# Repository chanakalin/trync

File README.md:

# trync
**trync** is an open source IoT powered application for logging environmetal conditions and maintaining saturated environmental conditions in medical storage and transporation.

More details available at [trync.blogspot.com](https://trync.blogspot.com)

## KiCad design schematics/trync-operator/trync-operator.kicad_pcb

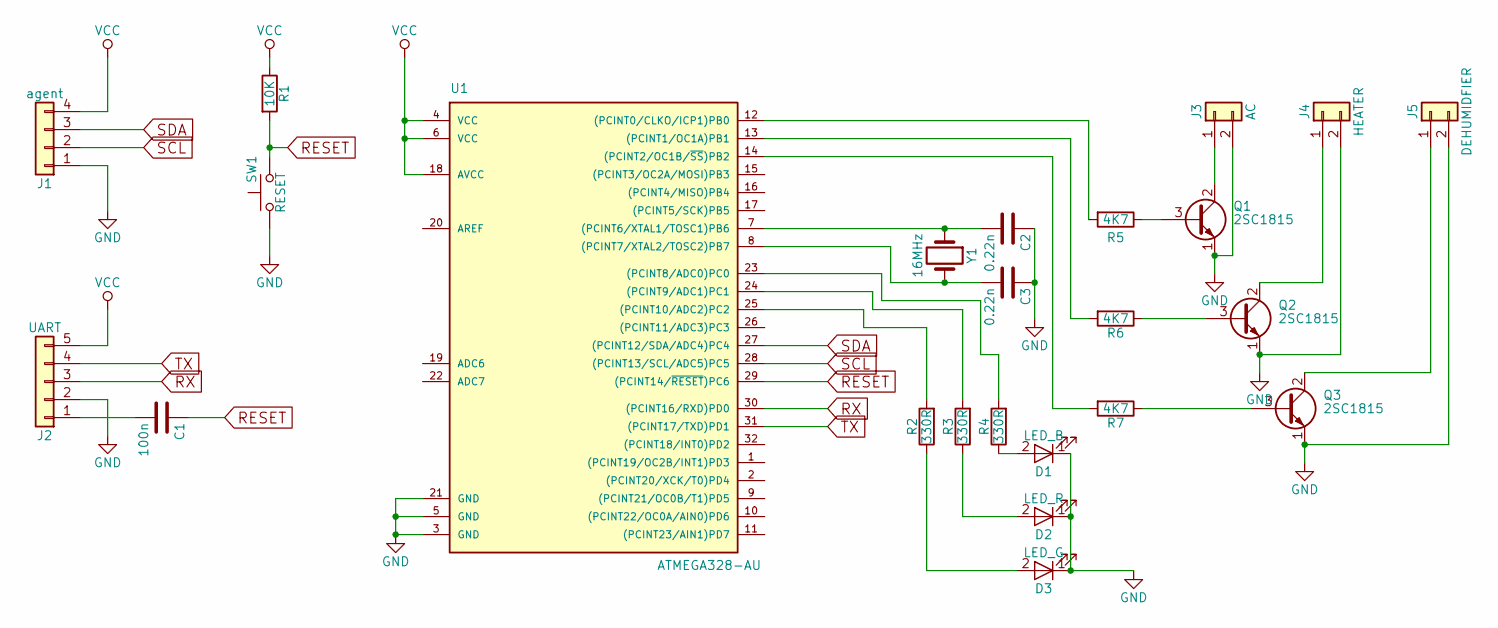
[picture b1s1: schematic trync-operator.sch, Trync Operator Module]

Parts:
C1: 100n; C_Disc_D4.3mm_W1.9mm_P5.00mm
C2, C3: 0.22n; C_Disc_D3.8mm_W2.6mm_P2.50mm
D1: LED_B; LED_0805_HandSoldering
D2: LED_R; LED_0805_HandSoldering
D3: LED_G; LED_0805_HandSoldering
J1: agent; Pin_Header_Straight_1x04_Pitch2.54mm
J2: UART; Pin_Header_Straight_1x05_Pitch2.54mm
J3: AC; Pin_Header_Angled_1x02_Pitch2.54mm
J4: HEATER; Pin_Header_Angled_1x02_Pitch2.54mm
J5: DEHUMIDFIER; Pin_Header_Angled_1x02_Pitch2.54mm
Q1, Q2, Q3: 2SC1815; TO-92_Molded_Narrow
R1: 10K; R_0805_HandSoldering
R2, R3, R4: 330R; R_0805_HandSoldering
R5, R6, R7: 4K7; R_0805_HandSoldering
SW1: RESET; SW_PUSH_6mm
U1: ATMEGA328-AU; TQFP-32_7x7mm_Pitch0.8mm
Y1: 16MHz; Crystal_HC52-8mm_Vertical

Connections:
GND: C2.1, C3.1, D1.1 (K), D2.1 (K), D3.1 (K), J1.1, J2.2, J3.2, J4.2, J5.2, Q1.1 (E), Q2.1 (E), Q3.1 (E), SW1.1, U1.3 (GND), U1.5 (GND), U1.21 (GND)
unnamed: C1.2, J2.1
unnamed: C2.2, U1.7 ((PCINT6/XTAL1/TOSC1)PB6), Y1.1
unnamed: C3.2, U1.8 ((PCINT7/XTAL2/TOSC2)PB7), Y1.2
unnamed: D1.2 (A), R4.1
unnamed: D2.2 (A), R3.1
unnamed: D3.2 (A), R2.1
unnamed: J3.1, Q1.2 (C)
unnamed: J4.1, Q2.2 (C)
unnamed: J5.1, Q3.2 (C)
unnamed: Q1.3 (B), R5.1
unnamed: Q2.3 (B), R6.1
unnamed: Q3.3 (B), R7.1
unnamed: R2.2, U1.25 ((PCINT10/ADC2)PC2)
unnamed: R3.2, U1.24 ((PCINT9/ADC1)PC1)
unnamed: R4.2, U1.23 ((PCINT8/ADC0)PC0)
unnamed: R5.2, U1.12 ((PCINT0/CLKO/ICP1)PB0)
unnamed: R6.2, U1.13 ((PCINT1/OC1A)PB1)
unnamed: R7.2, U1.14 ((PCINT2/OC1B/~SS~)PB2)
RESET: C1.1, R1.2, SW1.2, U1.29 ((PCINT14/~RESET~)PC6)
RX: J2.3, U1.30 ((PCINT16/RXD)PD0)
SCL: J1.2, U1.28 ((PCINT13/SCL/ADC5)PC5)
SDA: J1.3, U1.27 ((PCINT12/SDA/ADC4)PC4)
TX: J2.4, U1.31 ((PCINT17/TXD)PD1)
VCC: J1.4, J2.5, R1.1, U1.4 (VCC), U1.6 (VCC), U1.18 (AVCC)

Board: 2 copper layers, 24 parts (0 on the bottom side), 25 nets, no tracks yet.

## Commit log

2018-03-15 beta release - incomplete
2018-03-15 beta release - not-completed
2018-03-15 Beta - Not completed - Database backup added
